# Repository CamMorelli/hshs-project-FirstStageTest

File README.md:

# crisp teensy project

## Getting started

To make it easy for you to get started with GitLab, here's a list of recommended next steps.

Already a pro? Just edit this README.md and make it your own. Want to make it easy? [Use the template at the bottom](#editing-this-readme)!

## Add your files

- [ ] [Create](https://docs.gitlab.com/ee/user/project/repository/web_editor.html#create-a-file) or [upload](https://docs.gitlab.com/ee/user/project/repository/web_editor.html#upload-a-file) files
- [ ] [Add files using the command line](https://docs.gitlab.com/ee/gitlab-basics/add-file.html#add-a-file-using-the-command-line) or push an existing Git repository with the following command:

```
cd existing_repo
git remote add origin https://gitlab.com/numentus-technologies/crisp-teensy-project.git
git branch -M main
git push -uf origin main
```

## Integrate with your tools

- [ ] [Set up project integrations](https://gitlab.com/numentus-technologies/crisp-teensy-project/-/settings/integrations)

## Collaborate with your team

- [ ] [Invite team members and collaborators](https://docs.gitlab.com/ee/user/project/members/)
- [ ] [Create a new merge request](https://docs.gitlab.com/ee/user/project/merge_requests/creating_merge_requests.html)
- [ ] [Automatically close issues from merge requests](https://docs.gitlab.com/ee/user/project/issues/managing_issues.html#closing-issues-automatically)
- [ ] [Enable merge request approvals](https://docs.gitlab.com/ee/user/project/merge_requests/approvals/)
- [ ] [Set auto-merge](https://docs.gitlab.com/ee/user/project/merge_requests/merge_when_pipeline_succeeds.html)

## Test and Deploy

Use the built-in continuous integration in GitLab.

- [ ] [Get started with GitLab CI/CD](https://docs.gitlab.com/ee/ci/quick_start/index.html)
- [ ] [Analyze your code for known vulnerabilities with Static Application Security Testing(SAST)](https://docs.gitlab.com/ee/user/application_security/sast/)
- [ ] [Deploy to Kubernetes, Amazon EC2, or Amazon ECS using Auto Deploy](https://docs.gitlab.com/ee/topics/autodevops/requirements.html)
- [ ] [Use pull-based deployments for improved Kubernetes management](https://docs.gitlab.com/ee/user/clusters/agent/)
- [ ] [Set up protected environments](https://docs.gitlab.com/ee/ci/environments/protected_environments.html)

***

# Editing this README

When you're ready to make this README your own, just edit this file and use the handy template below (or feel free to structure it however you want - this is just a starting point!). Thank you to [makeareadme.com](https://www.makeareadme.com/) for this template.

## Suggestions for a good README
Every project is different, so consider which of these sections apply to yours. The sections used in the template are suggestions for most open source projects. Also keep in mind that while a README can be too long and detailed, too long is better than too short. If you think your README is too long, consider utilizing another form of documentation rather than cutting out information.

## Name
Teensy interface for ASI Imaging CRISP autofocus module

## Description
Let people know what your project can do specifically. Provide context and add a link to any reference visitors might be unfamiliar with. A list of Features or a Background subsection can also be added here. If there are alternatives to your project, this is a good place to list differentiating factors.

## Badges
On some READMEs, you may see small images that convey metadata, such as whether or not all the tests are passing for the project. You can use Shields to add some to your README. Many services also have instructions for adding a badge.

## Visuals
Depending on what you are making, it can be a good idea to include screenshots or even a video (you'll frequently see GIFs rather than actual videos). Tools like ttygif can help, but check out Asciinema for a more sophisticated method.

## Installation
Within a particular ecosystem, there may be a common way of installing things, such as using Yarn, NuGet, or Homebrew. However, consider the possibility that whoever is reading your README is a novice and would like more guidance. Listing specific steps helps remove ambiguity and gets people to using your project as quickly as possible. If it only runs in a specific context like a particular programming language version or operating system or has dependencies that have to be installed manually, also add a Requirements subsection.

## Usage
Use examples liberally, and show the expected output if you can. It's helpful to have inline the smallest example of usage that you can demonstrate, while providing links to more sophisticated examples if they are too long to reasonably include in the README.

## Support
Tell people where they can go to for help. It can be any combination of an issue tracker, a chat room, an email address, etc.

## Roadmap
If you have ideas for releases in the future, it is a good idea to list them in the README.

## Contributing
State if you are open to contributions and what your requirements are for accepting them.

For people who want to make changes to your project, it's helpful to have some documentation on how to get started. Perhaps there is a script that they should run or some environment variables that they need to set. Make these steps explicit. These instructions could also be useful to your future self.

You can also document commands to lint the code or run tests. These steps help to ensure high code quality and reduce the likelihood that the changes inadvertently break something. Having instructions for running tests is especially helpful if it requires external setup, such as starting a Selenium server for testing in a browser.

## Authors and acknowledgment
Show your appreciation to those who have contributed to the project.

## License
For open source projects, say how it is licensed.

## Project status
If you have run out of energy or time for your project, put a note at the top of the README saying that development has slowed down or stopped completely. Someone may choose to fork your project or volunteer to step in as a maintainer or owner, allowing your project to keep going. You can also make an explicit request for maintainers.

# Cameron: These are my personal setups for VS Code and C++ thus far for documentation purposes.

# For the setup of VS Code, so far I have installed the following extensions:
Python
C/C++
C/C++ Extension Pack
C/C++ Themes
CMake
Cmake Tools
Doxygen Documentation Generator
Git Graph
GitLab Workflow
PlatformIO IDE
Pylance
Pylint
Python Debugger

# I then installed the following modules via pip using the command "pip install (module)":
numpy
matplotlib
pyserial **NOTE: for the import command to access pyserial, the command is as follows: "import serial" NOT "import pyserial"**

# For the setup of GitLab and GitHub, I signed into my Git account, and linked it to VS Code through the GitLab Workflow extension.
This allowed me to save my changes as my account and properly document it under GitGraph when a change is requested.
I then accessed the specific online (not local) repository via email granted access from the authorized user.
I continue to access the HSHS project via GitLab's website. (To first log in there will be a free trial button, of which, if you press, will being you to a sign in button in order to access your preexisting account)

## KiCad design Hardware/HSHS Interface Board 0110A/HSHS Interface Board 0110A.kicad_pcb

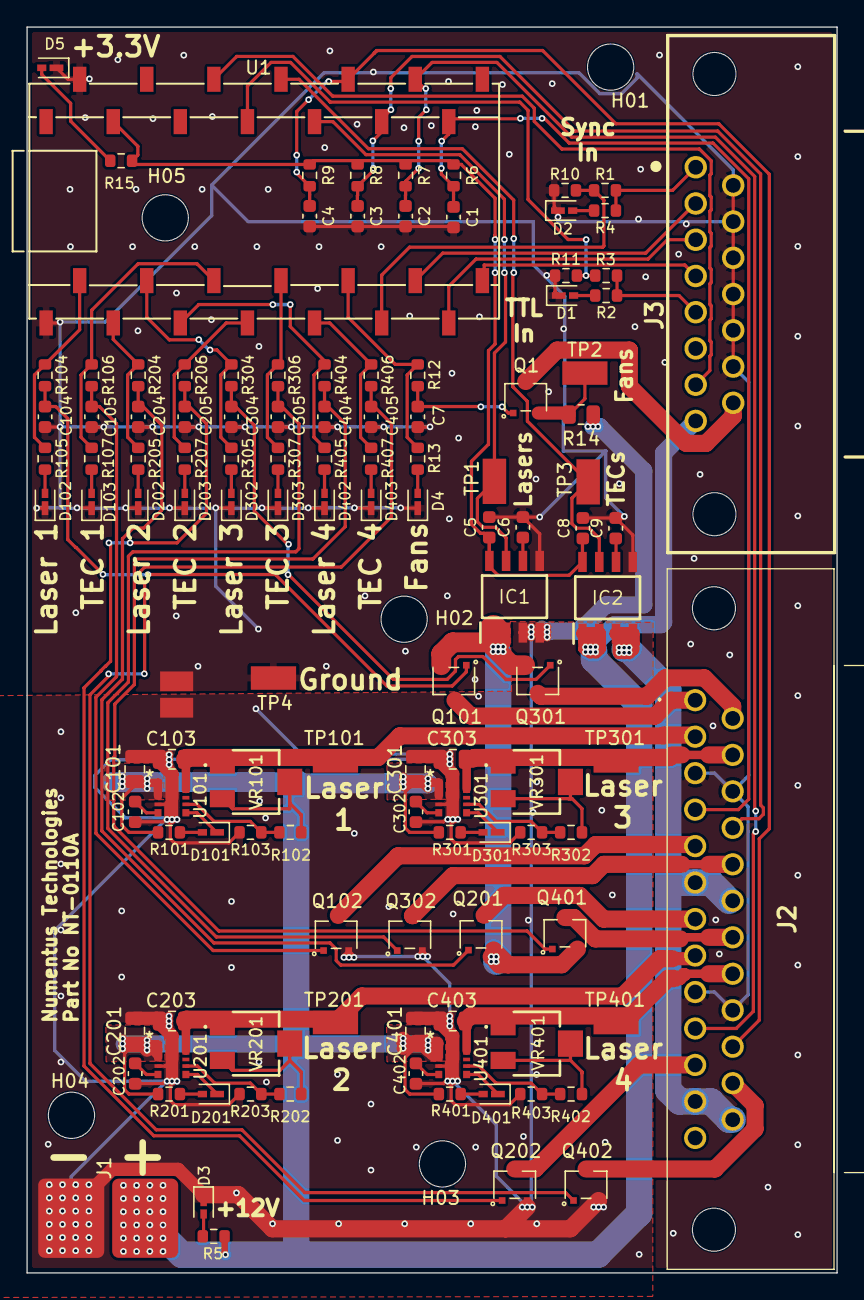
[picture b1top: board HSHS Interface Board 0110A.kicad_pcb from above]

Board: 2 copper layers, 61.3 x 94.3 mm, 126 parts (0 on the bottom side), 87 nets.

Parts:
C1, C2, C3, C4: 1µF; C_0603_1608Metric_Small_Font
C5, C8: 0.1µF; C_0603_1608Metric_Small_Font
C6, C9: 33nF; C_0603_1608Metric_Small_Font
C7, C102, C104, C105, C202, C204, C205, C302, C304, C305, C402, C404, C405: 10nF; C_0603_1608Metric_Small_Font
C101, C201, C301, C401: 10µF; C_0805_2012Metric
C103, C203, C303, C403: 22µF; C_0805_2012Metric
D1, D2, D3, D5: LED Green; AA1608 Generic Kingbrite LED
D4, D103, D203, D303, D403: LED Blue; AA1608 Generic Kingbrite LED
D101, D201, D301, D401: LED Red; AA1608 Generic Kingbrite LED
D102, D202, D302, D402: LED Yellow; AA1608 Generic Kingbrite LED
H01, H02, H03, H04, H05: MountingHole; MountingHole_3.5mm
IC1, IC2: ACS725LLCTR-10AU-T; SOIC127P600X175-8N
J1: Conn_01x02_Pin; Dual Solder Pads Both Sides No PTH
J2: 5788801-1; 57888011_A
J3: 5788798-1; 5788798-1 Fix_A
NT1: Solder Bridge; NetTieSolderBridgeSmaller
Q1, Q101, Q102, Q201, Q202, Q301, Q302, Q401, Q402: SSM3K376R_A; SSM3K376R_Mod_A
R1, R3, R13, R105, R107, R205, R207, R305, R307, R405, R407: 500; R_0603_1608Metric_Small_Font
R2, R4, R10, R11, R15: 1k; R_0603_1608Metric_Small_Font
R5, R102, R202, R302, R402: 25k; R_0603_1608Metric_Small_Font
R6, R7, R8, R9, R12, R104, R106, R204, R206, R304, R306, R404, R406: 10k; R_0603_1608Metric_Small_Font
R14: 0.1; R_0805_2012Metric
R101, R103, R201, R203, R301, R303, R401, R403: 15k; R_0603_1608Metric_Small_Font
TP1, TP2, TP3, TP4, TP101, TP201, TP301, TP401: 5015; KEYSTONE_5015
U1: Teensy4.0_28_Pins; Teensy40_with_3D_Model_28_Pins_Surface_Mount_C
U101, U201, U301, U401: TPSM82902SISR; uSIP11_SIS_TEX_Mod
VR101, VR201, VR301, VR401: SM-42X104; SM42X104_Smaller_Courtyard

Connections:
+3.3V: C5.1, C8.1, IC1.8 (VCC), IC2.8 (VCC), R6.1, R7.1, R8.1, R9.1, R15.1, U1.3V3
+12V: C101.1, C201.1, C301.1, C401.1, IC2.1 (IP+_1), IC2.2 (IP+_2), J1.1, J3.8, R5.1, R101.1, R201.1, R301.1, R401.1, U101.1 (VIN), U101.2 (VIN), U101.3 (EN), U201.1 (VIN), U201.2 (VIN), U201.3 (EN), U301.1 (VIN), U301.2 (VIN), U301.3 (EN), U401.1 (VIN), U401.2 (VIN), U401.3 (EN)
/Camera A+: J3.2, U1.10 (10_CS_MQSR)
/Camera B+: J3.3, U1.11 (11_MOSI_CTX1)
/Camera C+: J3.4, U1.12 (12_MISO_MQSL)
/Clock3.3V+: R1.2, R10.1, U1.9 (9_OUT1C)
/Clock5V+: J3.1, R1.1, R4.1
/Fan-: J3.15, Q1.3 (D)
/FanControl: R12.1, R13.1, U1.8 (8_TX2_IN1)
/Laser Monitor: IC1.7 (VIOUT), TP1.TP, U1.18 (18_A4_SDA0)
/LaserControl1: R104.1, R105.1, U1.0 (0_RX1_CRX2_CS1)
/LaserControl2: R204.1, R205.1, U1.1 (1_TX1_CTX2_MISO1)
/LaserControl3: R304.1, R305.1, U1.2 (2_OUT2)
/LaserControl4: R404.1, R405.1, U1.3 (3_LRCLK2)
/LaserPow1+: C103.1, J2.2, TP101.TP, U101.9 (VOUT), U101.10 (VOUT), VR101.1 (CCW)
/LaserPow1-: J2.1, Q101.3 (D)
/LaserPow2+: C203.1, J2.8, TP201.TP, U201.9 (VOUT), U201.10 (VOUT), VR201.1 (CCW)
/LaserPow2-: J2.7, Q201.3 (D)
/LaserPow3+: C303.1, J2.15, TP301.TP, U301.9 (VOUT), U301.10 (VOUT), VR301.1 (CCW)
/LaserPow3-: J2.14, Q301.3 (D)
/LaserPow4+: C403.1, J2.21, TP401.TP, U401.9 (VOUT), U401.10 (VOUT), VR401.1 (CCW)
/LaserPow4-: J2.20, Q401.3 (D)
/Spare+: J3.7, U1.21 (21_A7_RX5_BCLK1)
/TEC High: IC2.3 (IP-_1), IC2.4 (IP-_2), J2.6, J2.12, J2.19, J2.25
/TEC Monitor: IC2.7 (VIOUT), TP3.TP, U1.19 (19_A5_SCL0)
/TECControl1: R106.1, R107.1, U1.4 (4_BCLK2)
/TECControl2: R206.1, R207.1, U1.5 (5_IN2)
/TECControl3: R306.1, R307.1, U1.6 (6_OUT1D)
/TECControl4: R406.1, R407.1, U1.7 (7_RX2_OUT1A)
/TECPow1-: J2.5, Q102.3 (D)
/TECPow2-: J2.11, Q202.3 (D)
/TECPow3-: J2.18, Q302.3 (D)
/TECPow4-: J2.24, Q402.3 (D)
/TTLOut3.3V+: R3.2, R11.1, U1.20 (20_A6_TX5_LRCLK1)
/TTLOut5V+: J3.5, R2.1, R3.1
/Therm1+: C1.1, J2.4, R6.2, U1.14 (14_A0_TX3_SPDIF_OUT)
/Therm2+: C2.1, J2.10, R7.2, U1.15 (15_A1_RX3_SPDIF_IN)
/Therm3+: C3.1, J2.17, R8.2, U1.16 (16_A2_RX4_SCL1)
/Therm4+: C4.1, J2.23, R9.2, U1.17 (17_A3_TX4_SDA1)
GNDA: C1.2, C2.2, C3.2, C4.2, C5.2, C6.2, C7.2, C8.2, C9.2, C104.2, C105.2, C204.2, C205.2, C304.2, C305.2, C404.2, C405.2, D1.1 (K), D2.1 (K), D4.1 (K), D5.1 (K), D102.1 (K), D103.1 (K), D202.1 (K), D203.1 (K), D302.1 (K), D303.1 (K), D402.1 (K), D403.1 (K), IC1.5 (GND), IC2.5 (GND), J2.3, J2.9, J2.16, J2.22, J3.9, J3.10, J3.11, J3.12, J3.13, J3.14, NT1.1, R10.2, R11.2, TP4.TP, U1.G1 (GND), U1.G2 (GND)
GNDPWR: C101.2, C102.2, C103.2, C201.2, C202.2, C203.2, C301.2, C302.2, C303.2, C401.2, C402.2, C403.2, D3.1 (K), IC1.3 (IP-_1), IC1.4 (IP-_2), J1.2, NT1.2, Q102.2 (S), Q202.2 (S), Q302.2 (S), Q402.2 (S), R14.2, R103.2, R203.2, R303.2, R403.2, U101.4 (MODE/S-CONF), U101.11 (GND), U201.4 (MODE/S-CONF), U201.11 (GND), U301.4 (MODE/S-CONF), U301.11 (GND), U401.4 (MODE/S-CONF), U401.11 (GND)
Laser MOSFET Low: IC1.1 (IP+_1), IC1.2 (IP+_2), Q101.2 (S), Q201.2 (S), Q301.2 (S), Q401.2 (S)
unnamed: D1.2 (A), R2.2
unnamed: D2.2 (A), R4.2
unnamed: D3.2 (A), R5.2
unnamed: D4.2 (A), R13.2
unnamed: D5.2 (A), R15.2
unnamed: D101.2 (A), R101.2
unnamed: D101.1 (K), U101.6 (PG)
unnamed: D102.2 (A), R105.2
unnamed: D103.2 (A), R107.2
unnamed: D201.2 (A), R201.2
unnamed: D201.1 (K), U201.6 (PG)
unnamed: D202.2 (A), R205.2
unnamed: D203.2 (A), R207.2
unnamed: D301.2 (A), R301.2
unnamed: D301.1 (K), U301.6 (PG)
unnamed: D302.2 (A), R305.2
unnamed: D303.2 (A), R307.2
unnamed: D401.2 (A), R401.2
unnamed: D401.1 (K), U401.6 (PG)
unnamed: D402.2 (A), R405.2
unnamed: D403.2 (A), R407.2
unnamed: C6.1, IC1.6 (FILTER)
unnamed: C9.1, IC2.6 (FILTER)
unnamed: C7.1, Q1.1 (G), R12.2
unnamed: Q1.2 (S), R14.1, TP2.TP
unnamed: C104.1, Q101.1 (G), R104.2
unnamed: C105.1, Q102.1 (G), R106.2
unnamed: C204.1, Q201.1 (G), R204.2
unnamed: C205.1, Q202.1 (G), R206.2
unnamed: C304.1, Q301.1 (G), R304.2
unnamed: C305.1, Q302.1 (G), R306.2
unnamed: C404.1, Q401.1 (G), R404.2
unnamed: C405.1, Q402.1 (G), R406.2
unnamed: R102.1, R103.1, U101.7 (FB/VSET)
unnamed: C102.1, U101.5 (SS/TR)
unnamed: R202.1, R203.1, U201.7 (FB/VSET)
unnamed: C202.1, U201.5 (SS/TR)
unnamed: R302.1, R303.1, U301.7 (FB/VSET)
unnamed: C302.1, U301.5 (SS/TR)
unnamed: R402.1, R403.1, U401.7 (FB/VSET)
unnamed: C402.1, U401.5 (SS/TR)
unnamed: R102.2, VR101.2 (WIPER), VR101.3 (CW)
unnamed: R202.2, VR201.2 (WIPER), VR201.3 (CW)
unnamed: R302.2, VR301.2 (WIPER), VR301.3 (CW)
unnamed: R402.2, VR401.2 (WIPER), VR401.3 (CW)

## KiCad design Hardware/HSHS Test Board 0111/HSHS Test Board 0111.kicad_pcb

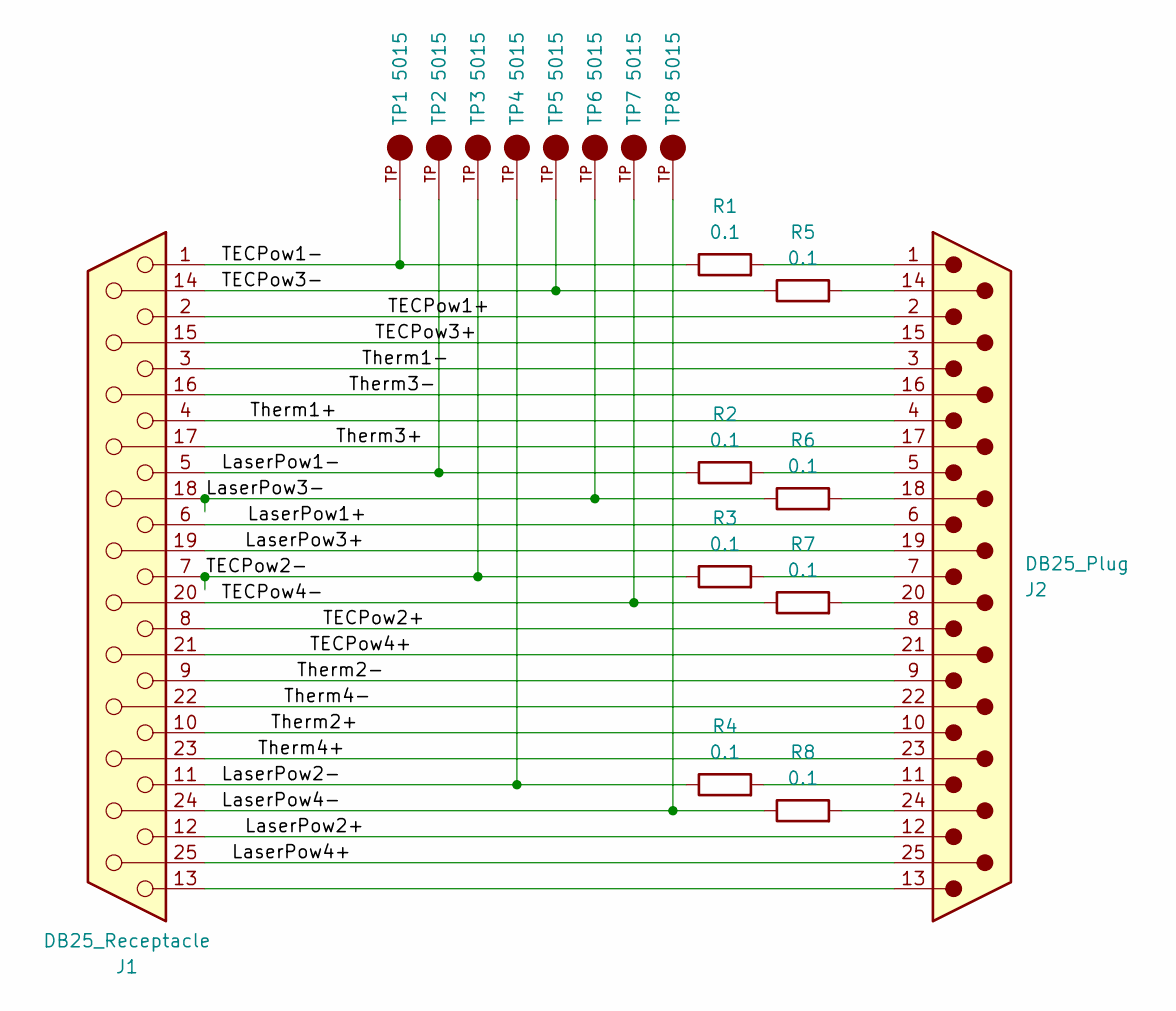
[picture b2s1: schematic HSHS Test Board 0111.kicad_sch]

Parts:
J1: DB25_Receptacle; 57888011_A; Manufacturer Part Number 5788801-1; Digikey_Part_Number A35139-ND
J2: DB25_Plug; 5788794_1 Mod From 57888011_A; Manufacturer Part Number 5788794-1; Digikey_Part_Number A35132-ND
R1, R2, R3, R4, R5, R6, R7, R8: 0.1; R_0805_2012Metric
TP1, TP2, TP3, TP4, TP5, TP6, TP7, TP8: 5015; KEYSTONE_5015; Manufacturer Part Number 5015; Digikey_Part_Number 36-5015CT-ND

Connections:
/LaserPow1+: J1.6, J2.6
/LaserPow1-: J1.5, R2.1, TP2.TP
/LaserPow2+: J1.12, J2.12
/LaserPow2-: J1.11, R4.1, TP4.TP
/LaserPow3+: J1.19, J2.19
/LaserPow3-: J1.18, R6.1, TP6.TP
/LaserPow4+: J1.25, J2.25
/LaserPow4-: J1.24, R8.1, TP8.TP
/TECPow1+: J1.2, J2.2
/TECPow1-: J1.1, R1.1, TP1.TP
/TECPow2+: J1.8, J2.8
/TECPow2-: J1.7, R3.1, TP3.TP
/TECPow3+: J1.15, J2.15
/TECPow3-: J1.14, R5.1, TP5.TP
/TECPow4+: J1.21, J2.21
/TECPow4-: J1.20, R7.1, TP7.TP
/Therm1+: J1.4, J2.4
/Therm1-: J1.3, J2.3
/Therm2+: J1.10, J2.10
/Therm2-: J1.9, J2.9
/Therm3+: J1.17, J2.17
/Therm3-: J1.16, J2.16
/Therm4+: J1.23, J2.23
/Therm4-: J1.22, J2.22
unnamed: J1.13, J2.13
unnamed: J2.14, R5.2
unnamed: J2.18, R6.2
unnamed: J2.20, R7.2
unnamed: J2.24, R8.2
unnamed: J2.1, R1.2
unnamed: J2.5, R2.2
unnamed: J2.7, R3.2
unnamed: J2.11, R4.2

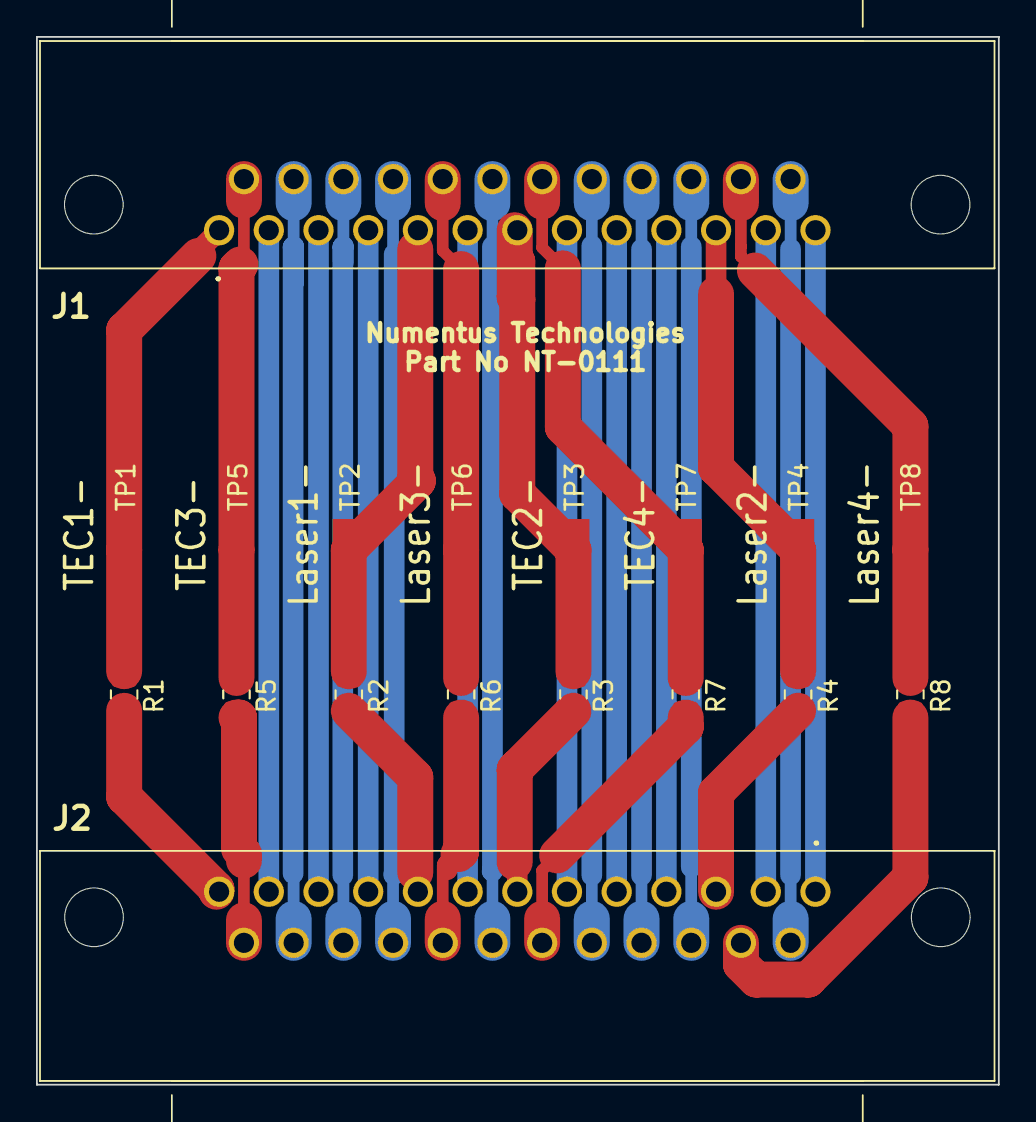
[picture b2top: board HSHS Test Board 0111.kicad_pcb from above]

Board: 2 copper layers, 53.4 x 58.2 mm, 18 parts (0 on the bottom side), 33 nets.

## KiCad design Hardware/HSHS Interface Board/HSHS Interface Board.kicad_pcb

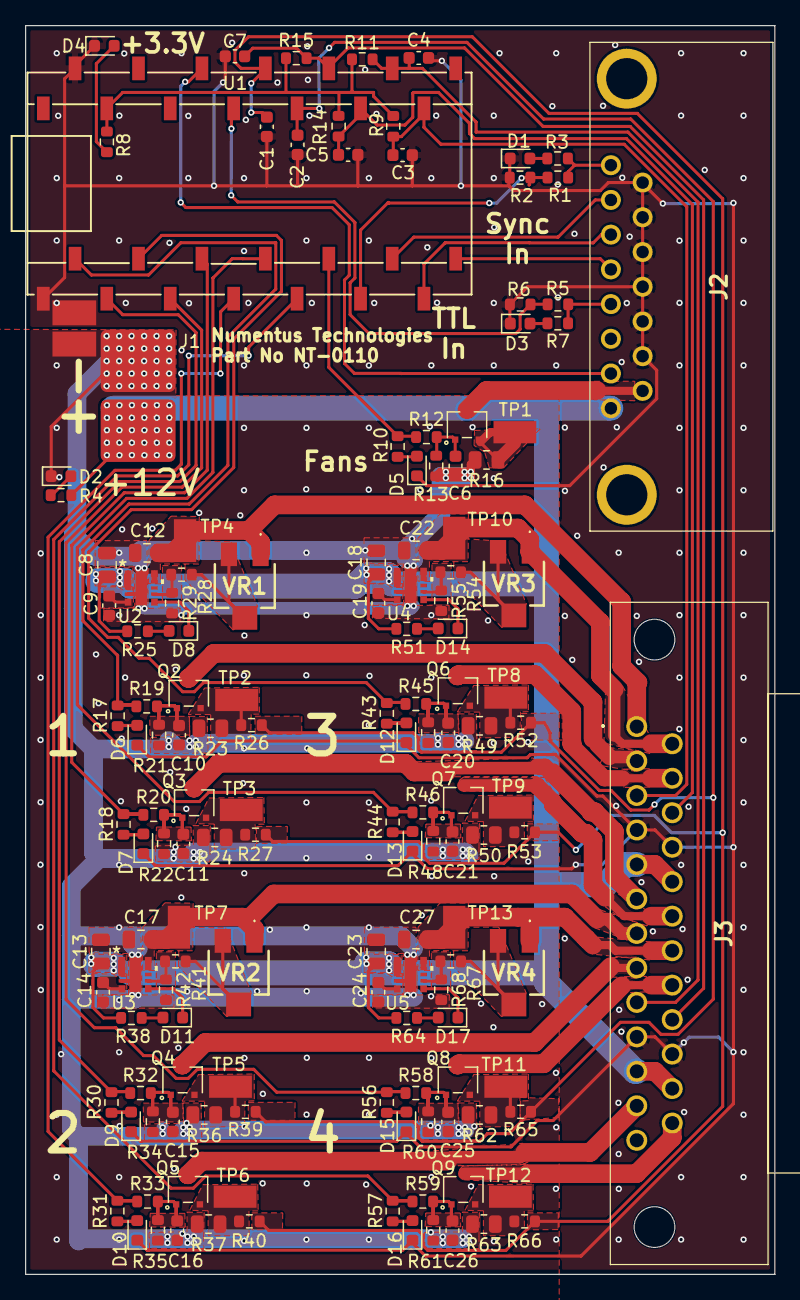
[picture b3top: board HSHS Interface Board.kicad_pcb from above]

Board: 2 copper layers, 60.0 x 100.0 mm, 147 parts (0 on the bottom side), 91 nets.

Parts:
C1, C2, C3, C4, C5, C7: 1µF; C_0603_1608Metric
C6, C9, C10, C11, C14, C15, C16, C19, C20, C21, C24, C25, C26: 10nF; C_0603_1608Metric
C8, C13, C18, C23: 10µF; C_0805_2012Metric
C12, C17, C22, C27: 22µF; C_0805_2012Metric
D1, D2, D3, D4: LED Green; D_0603_1608Metric
D5, D7, D10, D13, D16: LED Blue; D_0603_1608Metric
D6, D9, D12, D15: LED Yellow; D_0603_1608Metric
D8, D11, D14, D17: LED Red; D_0603_1608Metric
J1: Conn_01x02_Pin; Dual Solder Pads Both Sides No PTH
J2: 2301845-2; 23018452
J3: 5788801-1; 57888011
NT1: NetTie_2; NetTieSolderBridge
Q1, Q2, Q3, Q4, Q5, Q6, Q7, Q8, Q9: SSM3K376R_A; SSM3K376R_Mod_A
R1, R3, R5, R7, R8, R10, R17, R18, R30, R31, R43, R44, R56, R57: 500; R_0603_1608Metric
R2, R6: 1k; R_0603_1608Metric
R4, R9, R11, R12, R13, R14, R15, R19, R20, R21, R22, R26, R27, R32, R33, R34, R35, R39, R40, R45, R46, R47, R48, R52, R53, R58, R59, R60, R61, R65, R66: 10k; R_0603_1608Metric
R16, R23, R24, R36, R37, R49, R50, R62, R63: 0.1; R_0805_2012Metric
R25, R29, R38, R42, R51, R55, R64, R68: 15k; R_0603_1608Metric
R28, R41, R54, R67: 25k; R_0603_1608Metric
TP1, TP2, TP3, TP4, TP5, TP6, TP7, TP8, TP9, TP10, TP11, TP12, TP13: 5015; KEYSTONE_5015
U1: Teensy4.0_28_Pins; Teensy40_with_3D_Model_28_Pins_Surface_Mount_B
U2, U3, U4, U5: TPSM82902SISR; uSIP11_SIS_TEX
VR1, VR2, VR3, VR4: SM-42X104; SM42X104

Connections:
+3.3V: R8.1, R9.1, R11.1, R14.1, R15.1, U1.3V3
+12V: C8.1, C13.1, C18.1, C23.1, J1.1, J2.8, J3.5, J3.11, J3.18, J3.24, R4.1, R25.1, R38.1, R51.1, R64.1, U2.1 (VIN), U2.2 (VIN), U2.3 (EN), U3.1 (VIN), U3.2 (VIN), U3.3 (EN), U4.1 (VIN), U4.2 (VIN), U4.3 (EN), U5.1 (VIN), U5.2 (VIN), U5.3 (EN)
/Camera A+: J2.2, U1.10 (10_CS_MQSR)
/Camera B+: J2.3, U1.11 (11_MOSI_CTX1)
/Camera C+: J2.4, U1.12 (12_MISO_MQSL)
/Clock3.3V+: R1.2, R2.1, U1.9 (9_OUT1C)
/Clock5V+: J2.1, R1.1, R3.1
/Fan-: J2.15, Q1.3 (D)
/FanControl: R10.1, R12.1, U1.8 (8_TX2_IN1)
/LaserControl1: R17.1, R19.1, U1.0 (0_RX1_CRX2_CS1)
/LaserControl2: R30.1, R32.1, U1.1 (1_TX1_CTX2_MISO1)
/LaserControl3: R43.1, R45.1, U1.2 (2_OUT2)
/LaserControl4: R56.1, R58.1, U1.3 (3_LRCLK2)
/LaserPow1+: C12.1, J3.1, TP4.TP, U2.9 (VOUT), U2.10 (VOUT), VR1.1 (CCW)
/LaserPow1-: J3.2, Q2.3 (D)
/LaserPow2+: C17.1, J3.7, TP7.TP, U3.9 (VOUT), U3.10 (VOUT), VR2.1 (CCW)
/LaserPow2-: J3.8, Q4.3 (D)
/LaserPow3+: C22.1, J3.14, TP10.TP, U4.9 (VOUT), U4.10 (VOUT), VR3.1 (CCW)
/LaserPow3-: J3.15, Q6.3 (D)
/LaserPow4+: C27.1, J3.20, TP13.TP, U5.9 (VOUT), U5.10 (VOUT), VR4.1 (CCW)
/LaserPow4-: J3.21, Q8.3 (D)
/Spare+: J2.7, U1.21 (21_A7_RX5_BCLK1)
/TECControl1: R18.1, R20.1, U1.4 (4_BCLK2)
/TECControl2: R31.1, R33.1, U1.5 (5_IN2)
/TECControl3: R44.1, R46.1, U1.6 (6_OUT1D)
/TECControl4: R57.1, R59.1, U1.7 (7_RX2_OUT1A)
/TECPow1-: J3.6, Q3.3 (D)
/TECPow2-: J3.12, Q5.3 (D)
/TECPow3-: J3.19, Q7.3 (D)
/TECPow4-: J3.25, Q9.3 (D)
/TTLOut3.3V+: R5.2, R6.1, U1.20 (20_A6_TX5_LRCLK1)
/TTLOut5V+: J2.5, R5.1, R7.1
/Therm1+: C3.1, J3.3, R9.2, U1.14 (14_A0_TX3_SPDIF_OUT)
/Therm2+: C4.1, J3.9, R11.2, U1.15 (15_A1_RX3_SPDIF_IN)
/Therm3+: C5.1, J3.16, R14.2, U1.16 (16_A2_RX4_SCL1)
/Therm4+: C7.1, J3.22, R15.2, U1.17 (17_A3_TX4_SDA1)
GNDA: C1.2, C2.2, C3.2, C4.2, C5.2, C7.2, D1.1 (K), D3.1 (K), D4.1 (K), D5.1 (K), D6.1 (K), D7.1 (K), D9.1 (K), D10.1 (K), D12.1 (K), D13.1 (K), D15.1 (K), D16.1 (K), J2.9, J2.10, J2.11, J2.12, J2.13, J2.14, J3.4, J3.10, J3.17, J3.23, NT1.1, R2.2, R6.2, U1.G1 (GND), U1.G2 (GND)
GNDPWR: C6.2, C8.2, C9.2, C10.2, C11.2, C12.2, C13.2, C14.2, C15.2, C16.2, C17.2, C18.2, C19.2, C20.2, C21.2, C22.2, C23.2, C24.2, C25.2, C26.2, C27.2, D2.1 (K), J1.2, NT1.2, R13.2, R16.2, R21.2, R22.2, R23.2, R24.2, R29.2, R34.2, R35.2, R36.2, R37.2, R42.2, R47.2, R48.2, R49.2, R50.2, R55.2, R60.2, R61.2, R62.2, R63.2, R68.2, U2.4 (MODE/S-CONF), U2.11 (GND), U3.4 (MODE/S-CONF), U3.11 (GND), U4.4 (MODE/S-CONF), U4.11 (GND), U5.4 (MODE/S-CONF), U5.11 (GND)
Laser Monitor: C2.1, R26.1, R39.1, R52.1, R65.1, U1.18 (18_A4_SDA0)
unnamed: D1.2 (A), R3.2
unnamed: D2.2 (A), R4.2
unnamed: D3.2 (A), R7.2
unnamed: D4.2 (A), R8.2
unnamed: D5.2 (A), R10.2
unnamed: D6.2 (A), R17.2
unnamed: D7.2 (A), R18.2
unnamed: D8.2 (A), R25.2
unnamed: D8.1 (K), U2.6 (PG)
unnamed: D9.2 (A), R30.2
unnamed: D10.2 (A), R31.2
unnamed: D11.2 (A), R38.2
unnamed: D11.1 (K), U3.6 (PG)
unnamed: D12.2 (A), R43.2
unnamed: D13.2 (A), R44.2
unnamed: D14.2 (A), R51.2
unnamed: D14.1 (K), U4.6 (PG)
unnamed: D15.2 (A), R56.2
unnamed: D16.2 (A), R57.2
unnamed: D17.2 (A), R64.2
unnamed: D17.1 (K), U5.6 (PG)
unnamed: C6.1, Q1.1 (G), R12.2, R13.1
unnamed: Q1.2 (S), R16.1, TP1.TP
unnamed: C10.1, Q2.1 (G), R19.2, R21.1
unnamed: Q2.2 (S), R23.1, R26.2, TP2.TP
unnamed: C11.1, Q3.1 (G), R20.2, R22.1
unnamed: Q3.2 (S), R24.1, R27.2, TP3.TP
unnamed: C15.1, Q4.1 (G), R32.2, R34.1
unnamed: Q4.2 (S), R36.1, R39.2, TP5.TP
unnamed: C16.1, Q5.1 (G), R33.2, R35.1
unnamed: Q5.2 (S), R37.1, R40.2, TP6.TP
unnamed: C20.1, Q6.1 (G), R45.2, R47.1
unnamed: Q6.2 (S), R49.1, R52.2, TP8.TP
unnamed: C21.1, Q7.1 (G), R46.2, R48.1
unnamed: Q7.2 (S), R50.1, R53.2, TP9.TP
unnamed: C25.1, Q8.1 (G), R58.2, R60.1
unnamed: Q8.2 (S), R62.1, R65.2, TP11.TP
unnamed: C26.1, Q9.1 (G), R59.2, R61.1
unnamed: Q9.2 (S), R63.1, R66.2, TP12.TP
unnamed: R28.1, R29.1, U2.7 (FB/VSET)
unnamed: C9.1, U2.5 (SS/TR)
unnamed: R41.1, R42.1, U3.7 (FB/VSET)
unnamed: C14.1, U3.5 (SS/TR)
unnamed: R54.1, R55.1, U4.7 (FB/VSET)
unnamed: C19.1, U4.5 (SS/TR)
unnamed: R67.1, R68.1, U5.7 (FB/VSET)
unnamed: C24.1, U5.5 (SS/TR)
unnamed: R28.2, VR1.2 (WIPER), VR1.3 (CW)
unnamed: R41.2, VR2.2 (WIPER), VR2.3 (CW)
unnamed: R54.2, VR3.2 (WIPER), VR3.3 (CW)
unnamed: R67.2, VR4.2 (WIPER), VR4.3 (CW)
TEC Monitor: C1.1, R27.1, R40.1, R53.1, R66.1, U1.19 (19_A5_SCL0)
